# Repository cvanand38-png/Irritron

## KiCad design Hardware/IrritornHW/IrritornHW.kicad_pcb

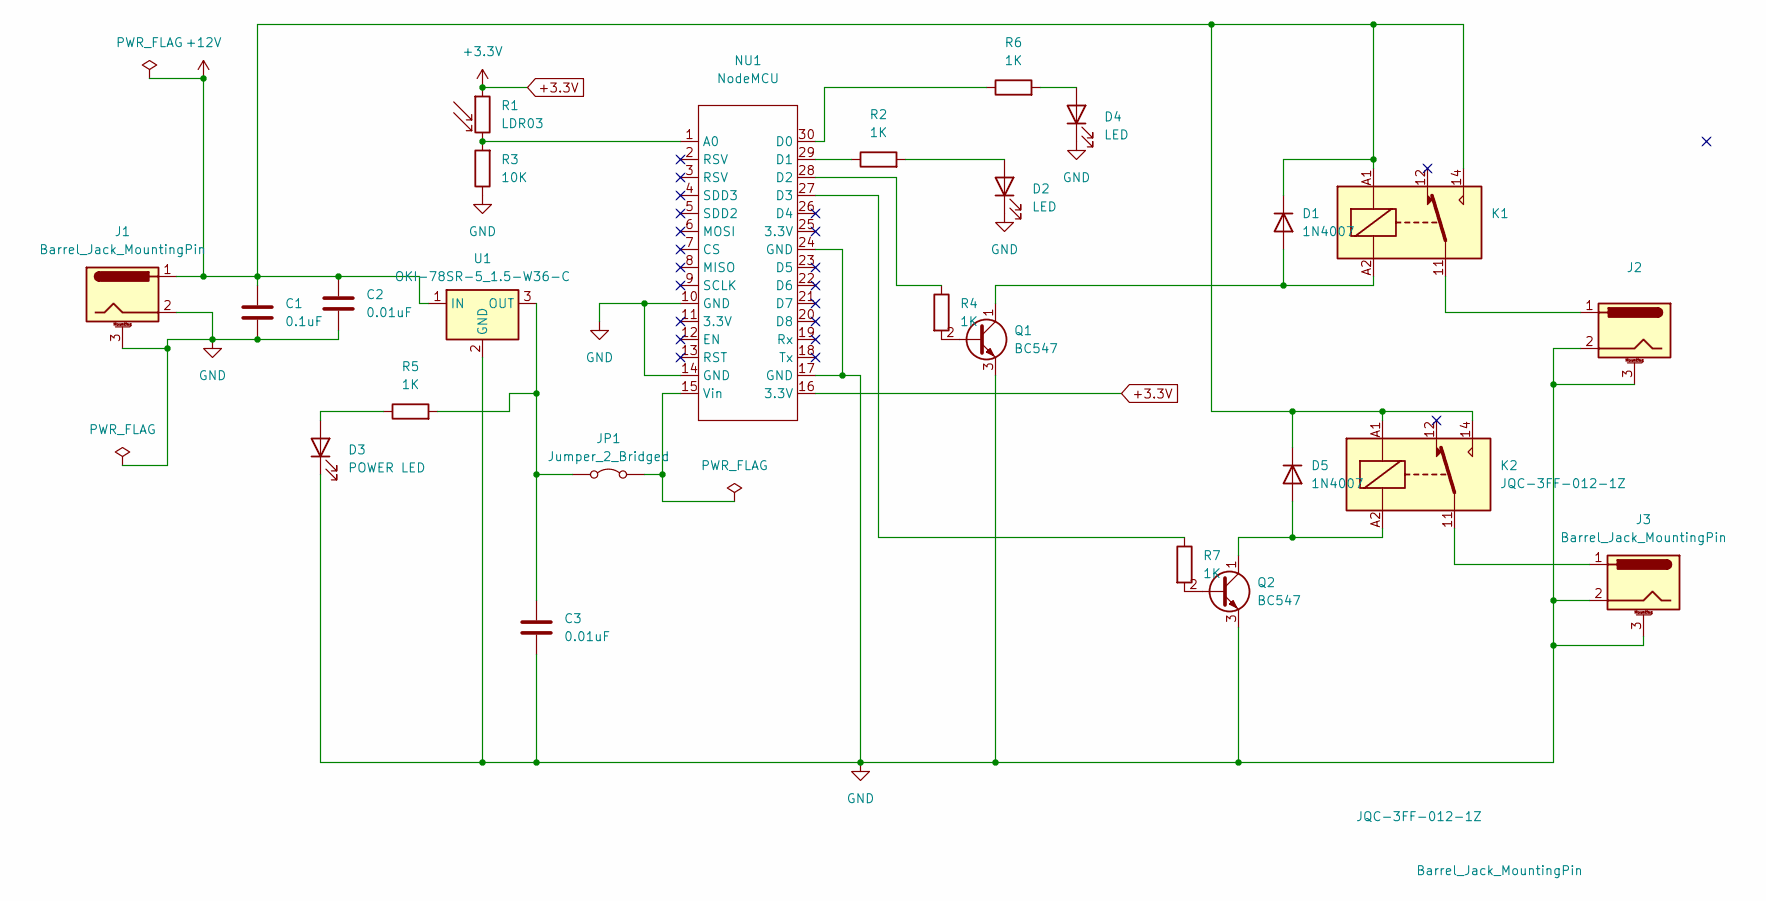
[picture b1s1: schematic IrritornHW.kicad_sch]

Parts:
C1: 0.1uF; C_Disc_D5.0mm_W2.5mm_P5.00mm
C2, C3: 0.01uF; C_Disc_D5.0mm_W2.5mm_P5.00mm
D1, D5: 1N4007; D_DO-41_SOD81_P10.16mm_Horizontal
D2, D4: LED; LED_D5.0mm
D3: POWER LED; LED_D5.0mm
J1, J2, J3: Barrel_Jack_MountingPin; BarrelJack_GCT_DCJ200-10-A_Horizontal
JP1: Jumper_2_Bridged; PinHeader_1x02_P2.54mm_Horizontal
K1, K2: JQC-3FF-012-1Z; Relay_SPDT_Hongfa_JQC-3FF_0XX-1Z
NU1: NodeMCU; NodeMCU_ESP8266_30PIN
Q1, Q2: BC547; TO-92_Inline
R1: LDR03; R_LDR_10x8.5mm_P7.6mm_Vertical
R2, R4, R5, R6, R7: 1K; R_Axial_DIN0207_L6.3mm_D2.5mm_P7.62mm_Horizontal
R3: 10K; R_Axial_DIN0207_L6.3mm_D2.5mm_P7.62mm_Horizontal
U1: OKI-78SR-5_1.5-W36-C; Converter_DCDC_Murata_OKI-78SR_Vertical

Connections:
+3.3V: NU1.16 (3.3V), R1.1
+12V: C1.1, C2.1, D1.1 (K), D5.1 (K), J1.1, K1.14, K1.A1, K2.14, K2.A1, U1.1 (IN)
GND: C1.2, C2.2, C3.2, D2.1 (K), D3.1 (K), D4.1 (K), J1.2, J1.3 (MountPin), J2.2, J2.3 (MountPin), J3.2, J3.3 (MountPin), NU1.10 (GND), NU1.14 (GND), NU1.17 (GND), NU1.24 (GND), Q1.3 (E), Q2.3 (E), R3.1, U1.2 (GND)
unnamed: D1.2 (A), K1.A2, Q1.1 (C)
unnamed: D2.2 (A), R2.2
unnamed: D3.2 (A), R5.1
unnamed: D4.2 (A), R6.2
unnamed: D5.2 (A), K2.A2, Q2.1 (C)
unnamed: J2.1, K1.11
unnamed: J3.1, K2.11
unnamed: C3.1, JP1.1 (A), R5.2, U1.3 (OUT)
unnamed: JP1.2 (B), NU1.15 (Vin)
unnamed: NU1.1 (A0), R1.2, R3.2
unnamed: NU1.30 (D0), R6.1
unnamed: NU1.29 (D1), R2.1
unnamed: NU1.28 (D2), R4.1
unnamed: NU1.27 (D3), R7.1
unnamed: Q1.2 (B), R4.2
unnamed: Q2.2 (B), R7.2

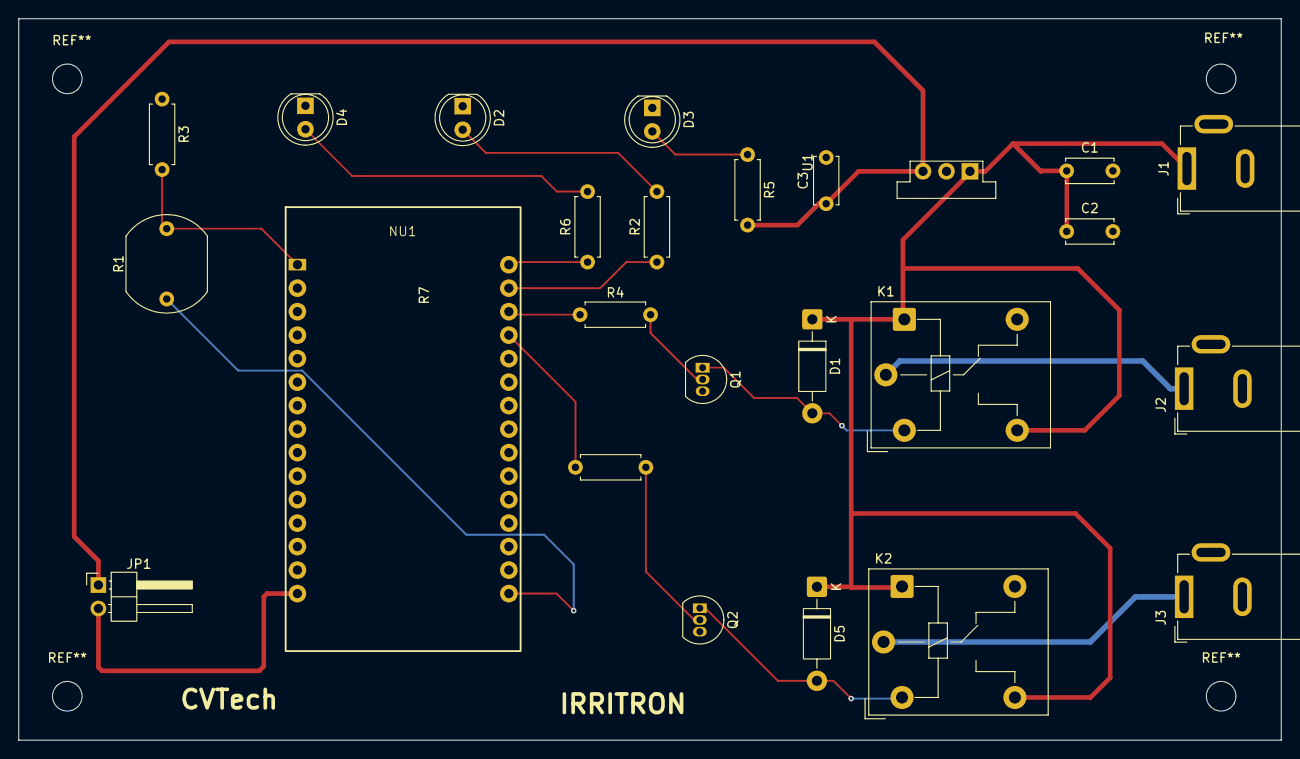
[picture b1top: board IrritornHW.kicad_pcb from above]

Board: 2 copper layers, 136.5 x 78.0 mm, 25 parts (0 on the bottom side), 19 nets.
